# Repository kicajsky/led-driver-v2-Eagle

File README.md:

# led-driver-v2-Eagle
Druga wersja projektu mająca na celu naprawę błędów wersji 1 i naukę nowego narzędzia Autodesk Eagle. Projekt zaliczeniowy kursu szkoleniowego.

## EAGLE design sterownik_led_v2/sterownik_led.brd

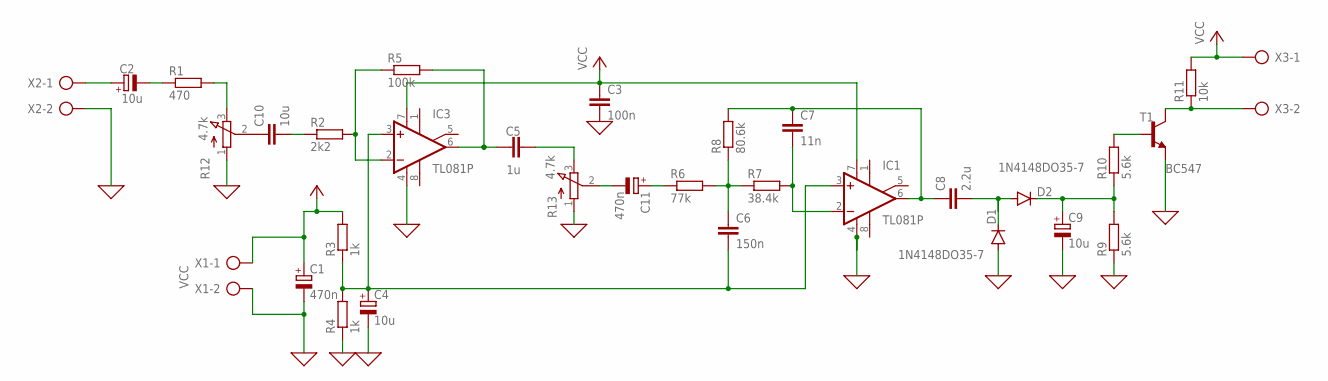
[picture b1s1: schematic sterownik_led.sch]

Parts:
C1, C11: 470n; TT2D7
C2, C4, C9: 10u; TT2D7
C3: 100n; C025-025X050
C5: 1u; C025-025X050
C6: 150n; C025-025X050
C7: 11n; C025-025X050
C8: 2.2u; C025-025X050
C10: 10u; C050-025X075
D1, D2: 1N4148DO35-7; DO35-7
IC1, IC3: TL081P; DIL08
R1: 470; 0207/10
R2: 2k2; 0207/10
R3, R4: 1k; 0207/10
R5: 100k; 0207/10
R6: 77k; 0207/10
R7: 38.4k; 0207/10
R8: 80.6k; 0207/10
R9, R10: 5.6k; 0207/10
R11: 10k; 0207/10
R12, R13: 4.7k; 3RP/1610N
T1: BC547; TO92
X1, X2, X3: AK500/2

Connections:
0: C1.-, C3.2, C4.-, C9.-, D1.A, IC1.4 (V-), IC3.4 (V-), R4.1, R9.1, R12.1 (A), R13.1 (A), T1.1 (E), X1.2, X2.2
JACK_VIN: C2.+, X2.1
unnamed: C4.+, C6.2, IC1.3 (+IN), IC3.3 (+IN), R3.1, R4.2
unnamed: R10.2, T1.2 (B)
unnamed: C10.1, R12.2 (S)
unnamed: C2.-, R1.1
unnamed: R1.2, R12.3 (E)
unnamed: C7.2, IC1.2 (-IN), R7.2
unnamed: C11.-, R13.2 (S)
unnamed: C5.1, IC3.6 (OUT), R5.2
unnamed: C6.1, R6.2, R7.1, R8.1
unnamed: C7.1, C8.1, IC1.6 (OUT), R8.2
unnamed: C8.2, D1.C, D2.A
unnamed: C9.+, D2.C, R9.2, R10.1
unnamed: C5.2, R13.3 (E)
unnamed: C10.2, R2.1
unnamed: C11.+, R6.1
unnamed: IC3.2 (-IN), R2.2, R5.1
OUT: R11.1, T1.3 (C), X3.2
VCC: C1.+, C3.1, IC1.7 (V+), IC3.7 (V+), R3.2, R11.2, X1.1, X3.1

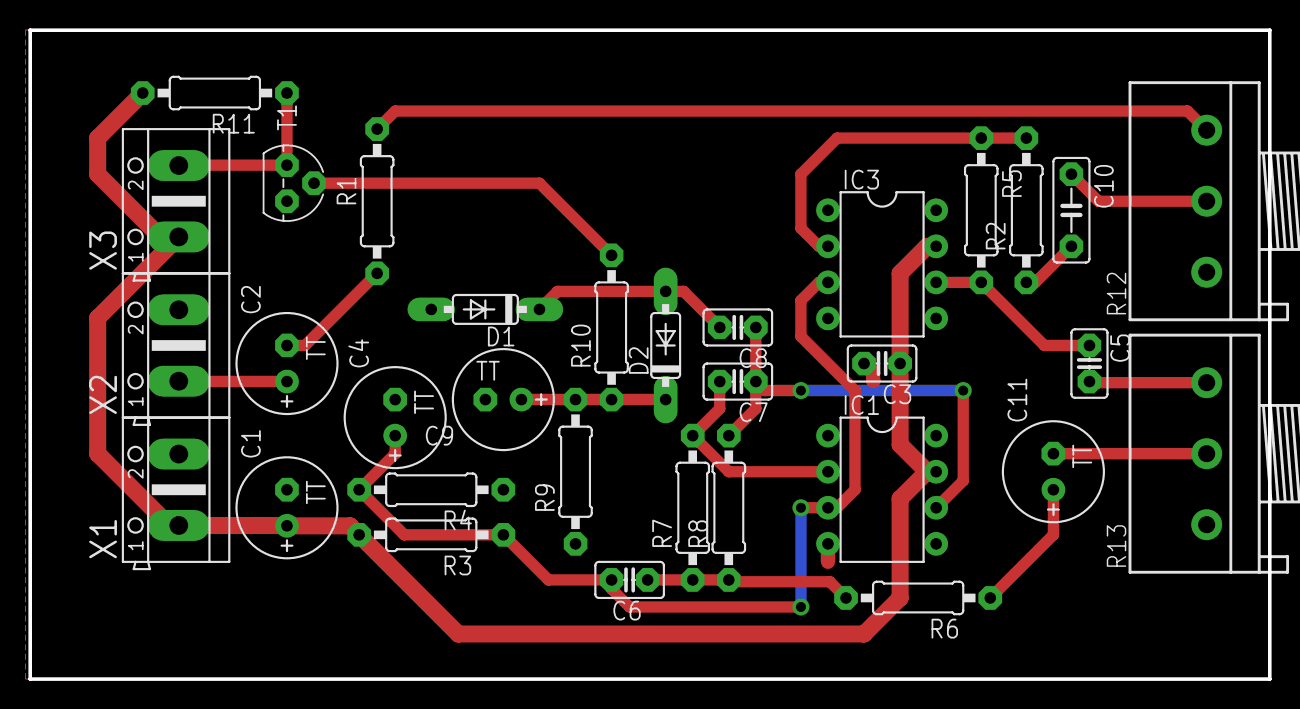
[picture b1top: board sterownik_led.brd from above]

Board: 2 copper layers, 87.3 x 45.7 mm, 32 parts (0 on the bottom side), 20 nets.

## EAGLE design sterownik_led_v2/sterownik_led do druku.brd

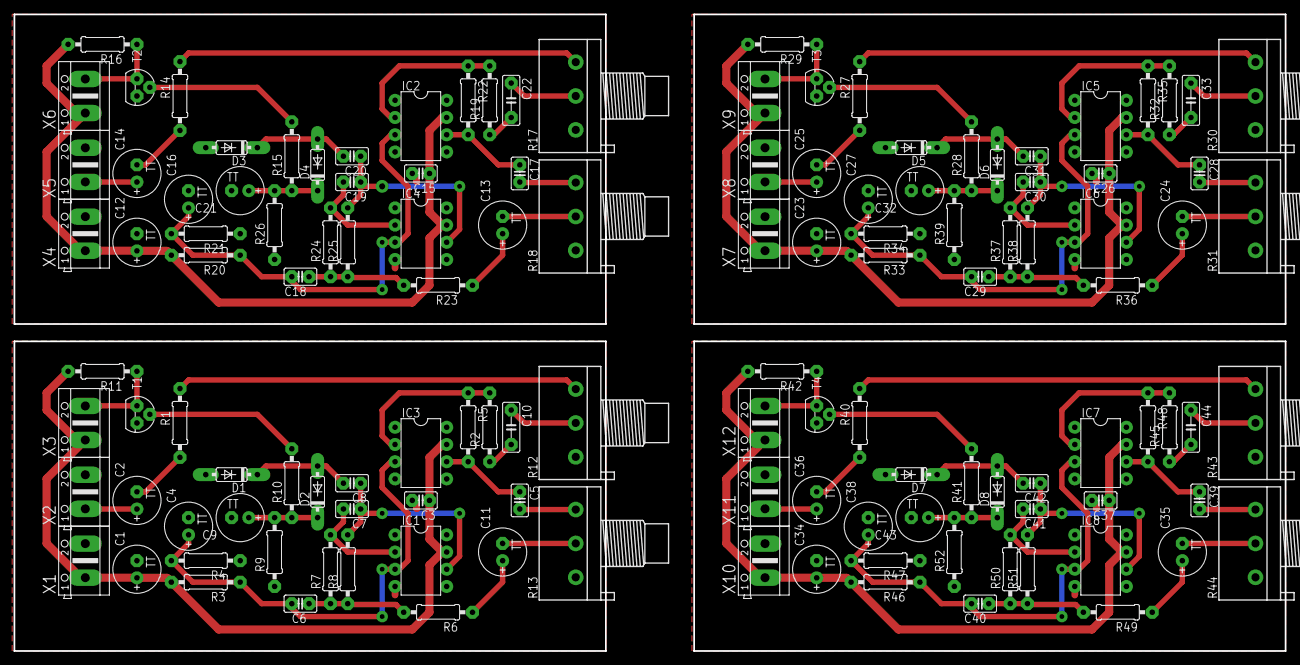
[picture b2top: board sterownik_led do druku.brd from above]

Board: 2 copper layers, 187.6 x 94.0 mm, 128 parts (0 on the bottom side), 80 nets.

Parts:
C1, C11, C12, C13, C23, C24, C34, C35: 470n; TT2D7
C2, C4, C9, C14, C16, C21, C25, C27, C32, C36, C38, C43: 10u; TT2D7
C3, C15, C26, C37: 100n; C025-025X050
C5, C17, C28, C39: 1u; C025-025X050
C6, C18, C29, C40: 150n; C025-025X050
C7, C19, C30, C41: 11n; C025-025X050
C8, C20, C31, C42: 2.2u; C025-025X050
C10, C22, C33, C44: 10u; C050-025X075
D1, D2, D3, D4, D5, D6, D7, D8: 1N4148DO35-7; DO35-7
IC1, IC2, IC3, IC4, IC5, IC6, IC7, IC8: TL081P; DIL08
R1, R14, R27, R40: 470; 0207/10
R2, R19, R32, R45: 2k2; 0207/10
R3, R4, R20, R21, R33, R34, R46, R47: 1k; 0207/10
R5, R22, R35, R48: 100k; 0207/10
R6, R23, R36, R49: 77k; 0207/10
R7, R24, R37, R50: 38.4k; 0207/10
R8, R25, R38, R51: 80.6k; 0207/10
R9, R10, R15, R26, R28, R39, R41, R52: 5.6k; 0207/10
R11, R16, R29, R42: 10k; 0207/10
R12, R13, R17, R18, R30, R31, R43, R44: 4.7k; 3RP/1610N
T1, T2, T3, T4: BC547; TO92
X1, X2, X3, X4, X5, X6, X7, X8, X9, X10, X11, X12: AK500/2

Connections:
0: C1.-, C3.2, C4.-, C9.-, D1.A, IC1.4, IC3.4, R4.1, R9.1, R12.1, R13.1, T1.1, X1.2, X2.2
1: C12.-, C15.2, C16.-, C21.-, D3.A, IC2.4, IC4.4, R17.1, R18.1, R21.1, R26.1, T2.1, X4.2, X5.2
2: C23.-, C26.2, C27.-, C32.-, D5.A, IC5.4, IC6.4, R30.1, R31.1, R34.1, R39.1, T3.1, X7.2, X8.2
3: C34.-, C37.2, C38.-, C43.-, D7.A, IC7.4, IC8.4, R43.1, R44.1, R47.1, R52.1, T4.1, X10.2, X11.2
JACK_VIN: C2.+, X2.1
JACK_VIN1: C14.+, X5.1
JACK_VIN2: C25.+, X8.1
JACK_VIN3: C36.+, X11.1
unnamed: C4.+, C6.2, IC1.3, IC3.3, R3.1, R4.2
unnamed: R10.2, T1.2
unnamed: C10.1, R12.2
unnamed: C2.-, R1.1
unnamed: R1.2, R12.3
unnamed: C7.2, IC1.2, R7.2
unnamed: C14.-, R14.1
unnamed: C11.-, R13.2
unnamed: C5.1, IC3.6, R5.2
unnamed: C6.1, R6.2, R7.1, R8.1
unnamed: C17.1, IC2.6, R22.2
unnamed: C7.1, C8.1, IC1.6, R8.2
unnamed: C18.1, R23.2, R24.1, R25.1
unnamed: C20.2, D3.C, D4.A
unnamed: C21.+, D4.C, R15.1, R26.2
unnamed: C8.2, D1.C, D2.A
unnamed: C9.+, D2.C, R9.2, R10.1
unnamed: C5.2, R13.3
unnamed: C10.2, R2.1
unnamed: C11.+, R6.1
unnamed: IC3.2, R2.2, R5.1
unnamed: R15.2, T2.2
unnamed: R14.2, R17.3
unnamed: C22.2, R19.1
unnamed: C17.2, R18.3
unnamed: C16.+, C18.2, IC2.3, IC4.3, R20.1, R21.2
unnamed: C13.-, R18.2
unnamed: C13.+, R23.1
unnamed: IC2.2, R19.2, R22.1
unnamed: C19.2, IC4.2, R24.2
unnamed: C19.1, C20.1, IC4.6, R25.2
unnamed: C22.1, R17.2
unnamed: C25.-, R27.1
unnamed: C28.1, IC5.6, R35.2
unnamed: C29.1, R36.2, R37.1, R38.1
unnamed: C31.2, D5.C, D6.A
unnamed: C32.+, D6.C, R28.1, R39.2
unnamed: R28.2, T3.2
unnamed: R27.2, R30.3
unnamed: C33.2, R32.1
unnamed: C28.2, R31.3
unnamed: C27.+, C29.2, IC5.3, IC6.3, R33.1, R34.2
unnamed: C24.-, R31.2
unnamed: C24.+, R36.1
unnamed: IC5.2, R32.2, R35.1
unnamed: C30.2, IC6.2, R37.2
unnamed: C30.1, C31.1, IC6.6, R38.2
unnamed: C33.1, R30.2
unnamed: C36.-, R40.1
unnamed: C39.1, IC7.6, R48.2
unnamed: C40.1, R49.2, R50.1, R51.1
unnamed: C42.2, D7.C, D8.A
unnamed: C43.+, D8.C, R41.1, R52.2
unnamed: R41.2, T4.2
unnamed: R40.2, R43.3
unnamed: C44.2, R45.1
unnamed: C39.2, R44.3
unnamed: C38.+, C40.2, IC7.3, IC8.3, R46.1, R47.2
unnamed: C35.-, R44.2
unnamed: C35.+, R49.1
unnamed: IC7.2, R45.2, R48.1
unnamed: C41.2, IC8.2, R50.2
unnamed: C41.1, C42.1, IC8.6, R51.2
unnamed: C44.1, R43.2
OUT: R11.1, T1.3, X3.2
OUT1: R16.1, T2.3, X6.2
OUT2: R29.1, T3.3, X9.2
OUT3: R42.1, T4.3, X12.2
VCC: C1.+, C3.1, IC1.7, IC3.7, R3.2, R11.2, X1.1, X3.1
VCC1: C12.+, C15.1, IC2.7, IC4.7, R16.2, R20.2, X4.1, X6.1
VCC2: C23.+, C26.1, IC5.7, IC6.7, R29.2, R33.2, X7.1, X9.1
VCC3: C34.+, C37.1, IC7.7, IC8.7, R42.2, R46.2, X10.1, X12.1
